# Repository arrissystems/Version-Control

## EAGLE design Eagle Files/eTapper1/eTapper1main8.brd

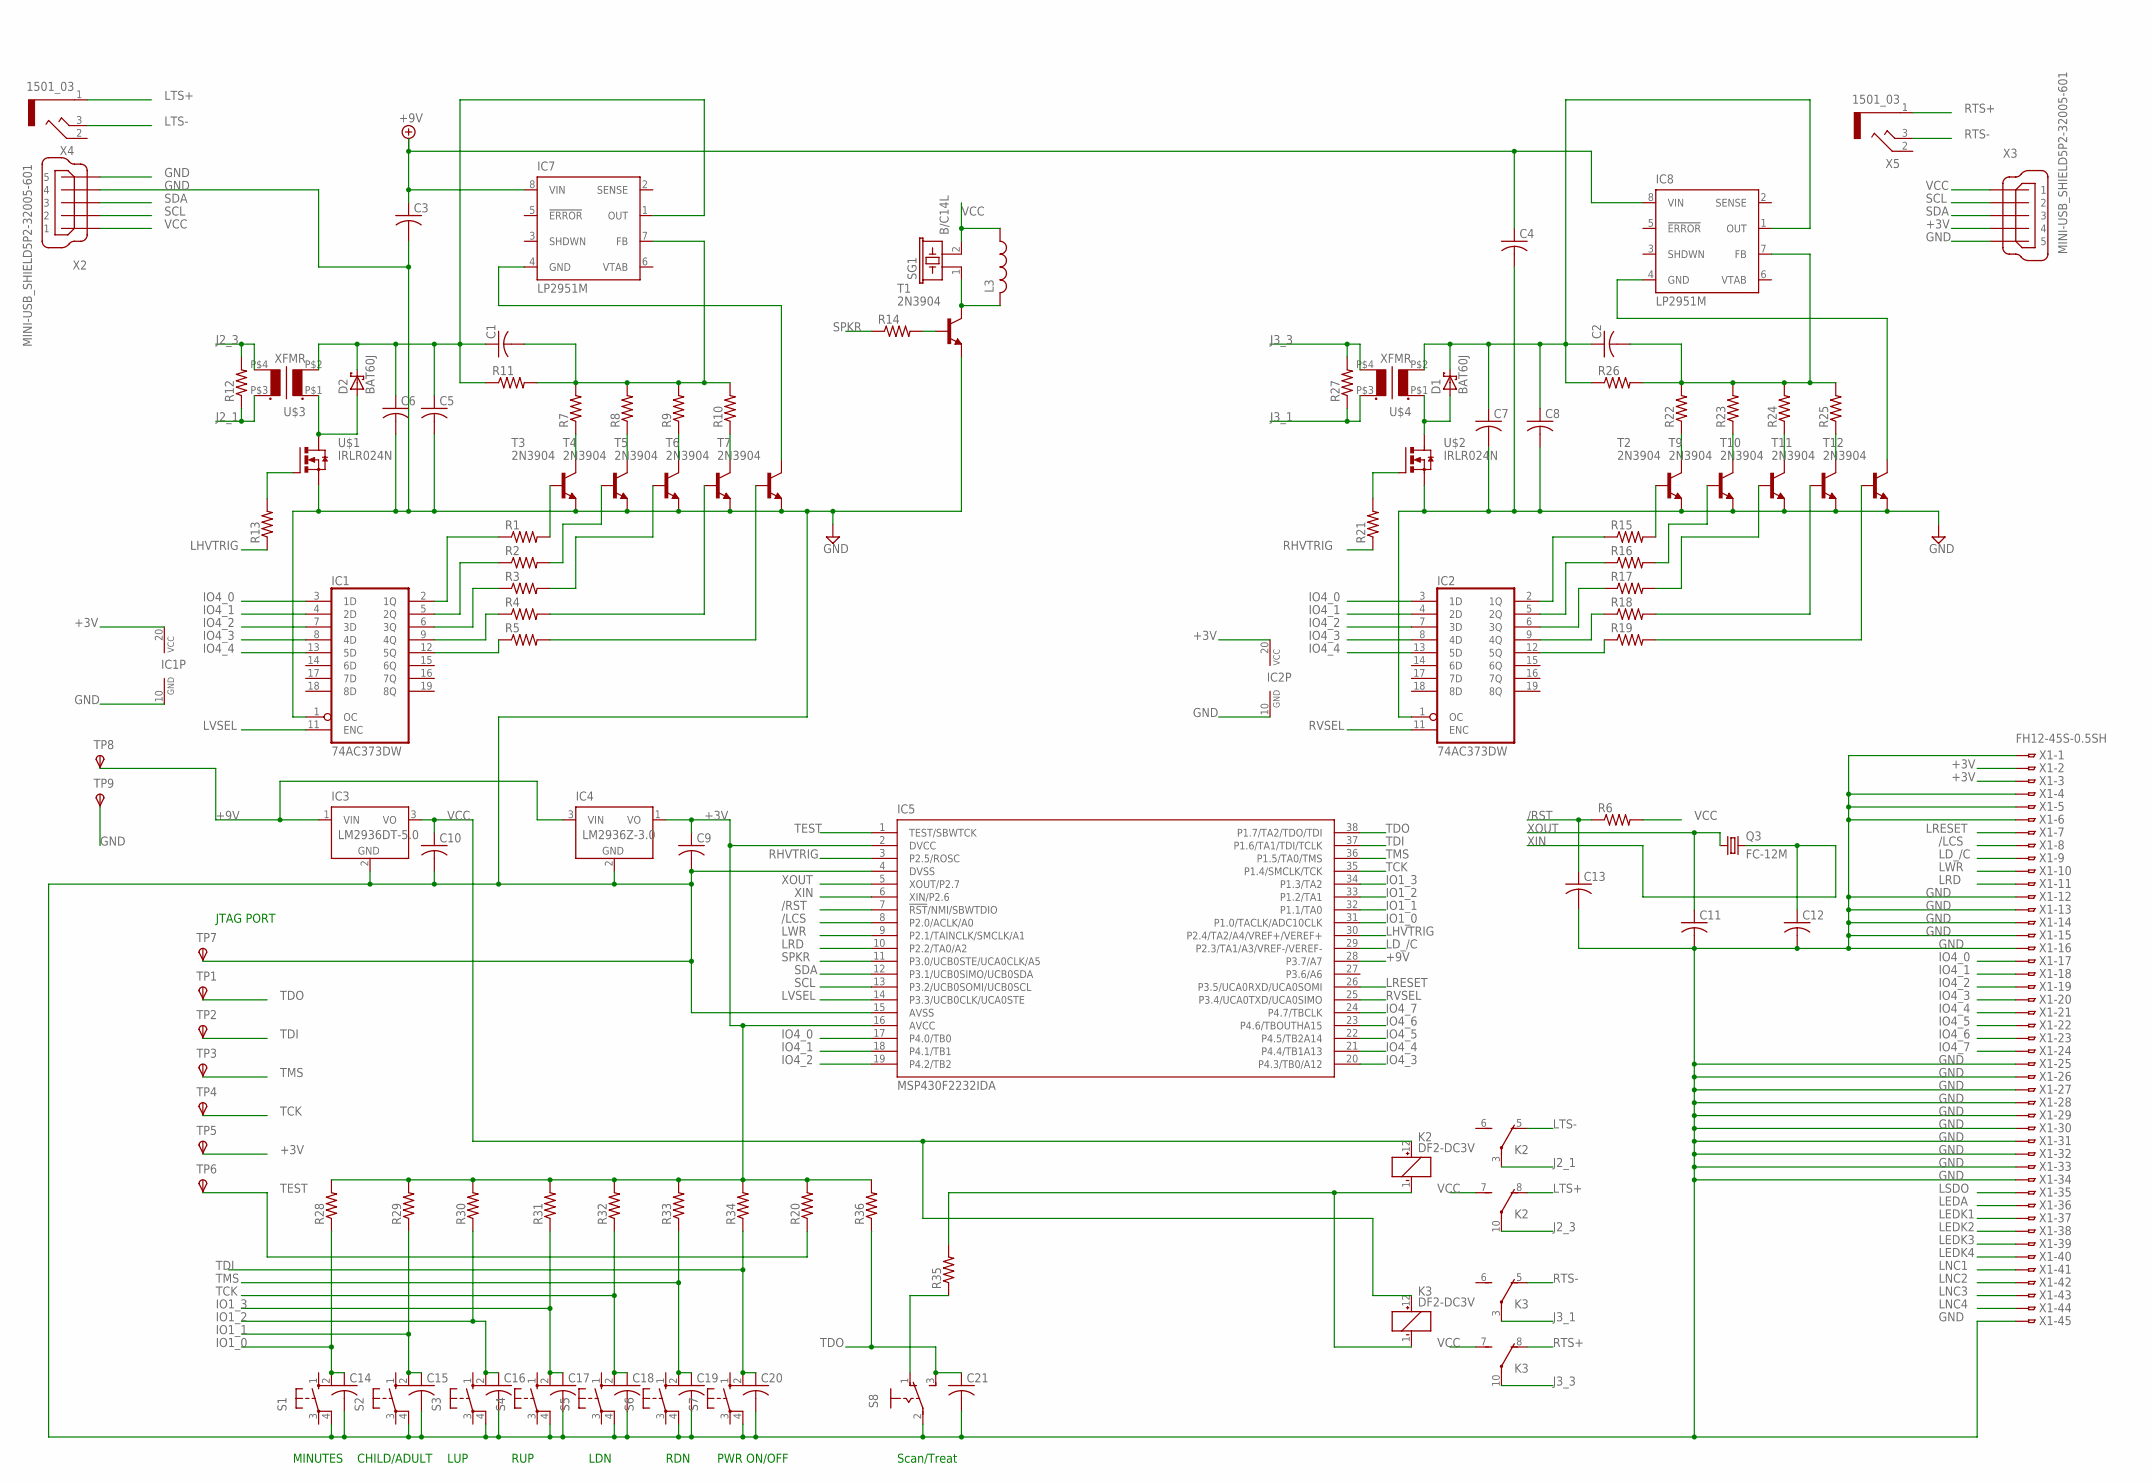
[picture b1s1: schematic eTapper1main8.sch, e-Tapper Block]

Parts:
C1, C2, C3, C4, C5, C6, C7, C8, C9, C10, C11, C12, C13, C14, C15, C16, C17, C18, C19, C20, C21: C-USC0805; C0805
D1, D2: BAT60J; SOD323_ST
IC1, IC2: 74AC373DW; SO20W
IC3: LM2936DT-5.0; TO252
IC4: LM2936Z-3.0; TO92
IC5: MSP430F2232IDA; TSSOP38_R-PDSO-G38-DA
IC7, IC8: LP2951M; SO08
K2, K3: DF2-DC3V; DF2
L3: L-USL2825P; L2825P
Q3: FC-12M
R1, R2, R3, R4, R5, R6, R7, R8, R9, R10, R11, R12, R13, R14, R15, R16, R17, R18, R19, R20, R21, R22, R23, R24, R25, R26, R27, R28, R29, R30, R31, R32, R33, R34, R35, R36: R-US_R0402; R0402
S1, S2, S3, S4, S5, S6, S7: 10-XX; B3F-10XX
S8: M251
SG1: B/C14L
T1, T2, T3, T4, T5, T6, T7, T9, T10, T11, T12: 2N3904; TO92
TP1, TP2, TP3, TP4, TP5, TP6, TP7, TP8, TP9: TPSTP06R; TP06R
U$1, U$2: IRLR024N; I-PAK_TO251AA
U$3, U$4: XFMR
X1: FH12-45S-0.5SH
X2, X3: MINI-USB_SHIELD5P2-32005-601; 32005-601
X4, X5: 1501_03

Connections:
+3V: C9.1, IC1.20 (VCC), IC2.20 (VCC), IC4.1 (VO), IC5.2 (DVCC), IC5.16 (AVCC), R20.2, R28.2, R29.2, R30.2, R31.2, R32.2, R33.2, R34.2, R36.2, TP5.TP, X1.2, X1.3, X3.4
+9V: C3.1, C4.1, IC3.1 (VIN), IC4.3 (VIN), IC5.28 (P3.7/A7), IC7.8 (VIN), IC8.8 (VIN), TP8.TP
/LCS: IC5.8 (P2.0/ACLK/A0), X1.8
/RST: C13.1, IC5.7 (!RST!/NMI/SBWTDIO), R6.1
GND: C3.2, C4.2, C5.2, C6.2, C7.2, C8.2, C9.2, C10.2, C11.2, C12.2, C13.2, C14.2, C15.2, C16.2, C17.2, C18.2, C19.2, C20.2, C21.2, IC1.1 (OC), IC1.10 (GND), IC2.1 (OC), IC2.10 (GND), IC3.2 (GND), IC4.2 (GND), IC5.4 (DVSS), IC5.15 (AVSS), S1.4 (P1), S2.4 (P1), S3.4 (P1), S4.4 (P1), S5.4 (P1), S6.4 (P1), S7.4 (P1), S8.2, T1.3 (E), T2.3 (E), T3.3 (E), T4.3 (E), T5.3 (E), T6.3 (E), T7.3 (E), T9.3 (E), T10.3 (E), T11.3 (E), T12.3 (E), TP7.TP, TP9.TP, U$1.3 (S), U$2.3 (S), X1.1, X1.4, X1.5, X1.6, X1.12, X1.13, X1.14, X1.15, X1.16, X1.25, X1.26, X1.27, X1.28, X1.29, X1.30, X1.31, X1.32, X1.33, X1.34, X1.45, X2.4, X2.5, X3.5
IO1_0: C14.1, IC5.31 (P1.0/TACLK/ADC10CLK), R28.1, S1.2 (S1)
IO1_1: C15.1, IC5.32 (P1.1/TA0), R29.1, S2.2 (S1)
IO1_2: C16.1, IC5.33 (P1.2/TA1), R30.1, S3.2 (S1)
IO1_3: C17.1, IC5.34 (P1.3/TA2), R31.1, S4.2 (S1)
IO4_0: IC1.3 (1D), IC2.3 (1D), IC5.17 (P4.0/TB0), X1.17
IO4_1: IC1.4 (2D), IC2.4 (2D), IC5.18 (P4.1/TB1), X1.18
IO4_2: IC1.7 (3D), IC2.7 (3D), IC5.19 (P4.2/TB2), X1.19
IO4_3: IC1.8 (4D), IC2.8 (4D), IC5.20 (P4.3/TB0/A12), X1.20
IO4_4: IC1.13 (5D), IC2.13 (5D), IC5.21 (P4.4/TB1A13), X1.21
IO4_5: IC5.22 (P4.5/TB2A14), X1.22
IO4_6: IC5.23 (P4.6/TBOUTHA15), X1.23
IO4_7: IC5.24 (P4.7/TBCLK), X1.24
J2_1: K2.3, R12.1, U$3.P$3 (S1)
J2_3: K2.10, R12.2, U$3.P$4 (S2)
J3_1: K3.3, R27.1, U$4.P$3 (S1)
J3_3: K3.10, R27.2, U$4.P$4 (S2)
LD_/C: IC5.29 (P2.3/TA1/A3/VREF-/VEREF-), X1.9
LEDA: X1.36
LEDK1: X1.37
LEDK2: X1.38
LEDK3: X1.39
LEDK4: X1.40
LHVTRIG: IC5.30 (P2.4/TA2/A4/VREF+/VEREF+), R13.1
LNC1: X1.41
LNC2: X1.42
LNC3: X1.43
LNC4: X1.44
LRD: IC5.10 (P2.2/TA0/A2), X1.11
LRESET: IC5.26 (P3.5/UCA0RXD/UCA0SOMI), X1.7
LSDO: X1.35
LTS+: K2.8 (O), X4.1
LTS-: K2.5 (O), X4.3
LVSEL: IC1.11 (ENC), IC5.14 (P3.3/UCB0CLK/UCA0STE)
LWR: IC5.9 (P2.1/TAINCLK/SMCLK/A1), X1.10
unnamed: IC1.2 (1Q), R1.1
unnamed: IC1.5 (2Q), R2.1
unnamed: IC1.6 (3Q), R3.1
unnamed: IC1.9 (4Q), R4.1
unnamed: IC1.12 (5Q), R5.1
unnamed: L3.2, SG1.1, T1.1 (C)
unnamed: R4.2, T6.2 (B)
unnamed: R5.2, T7.2 (B)
unnamed: D2.A, U$1.2 (D), U$1.4 (D), U$3.P$1 (P1)
unnamed: R7.1, T3.1 (C)
unnamed: R8.1, T4.1 (C)
unnamed: R9.1, T5.1 (C)
unnamed: R1.2, T3.2 (B)
unnamed: R2.2, T4.2 (B)
unnamed: R3.2, T5.2 (B)
unnamed: R10.1, T6.1 (C)
unnamed: C1.2, IC7.7 (FB), R7.2, R8.2, R9.2, R10.2, R11.2
unnamed: C1.1, C5.1, C6.1, D2.C, IC7.1 (OUT), R11.1, U$3.P$2 (P2)
unnamed: D1.A, U$2.2 (D), U$2.4 (D), U$4.P$1 (P1)
unnamed: IC2.2 (1Q), R15.1
unnamed: R13.2, U$1.1 (G)
unnamed: R14.2, T1.2 (B)
unnamed: R35.1, S8.1 (O)
unnamed: IC2.5 (2Q), R16.1
unnamed: IC2.6 (3Q), R17.1
unnamed: IC2.9 (4Q), R18.1
unnamed: IC2.12 (5Q), R19.1
unnamed: R15.2, T2.2 (B)
unnamed: R16.2, T9.2 (B)
unnamed: R17.2, T10.2 (B)
unnamed: R18.2, T11.2 (B)
unnamed: R19.2, T12.2 (B)
unnamed: K2.1 (-), K3.1 (-), R35.2
unnamed: R22.1, T2.1 (C)
unnamed: R23.1, T9.1 (C)
unnamed: R24.1, T10.1 (C)
unnamed: R25.1, T11.1 (C)
unnamed: C2.2, IC8.7 (FB), R22.2, R23.2, R24.2, R25.2, R26.2
unnamed: C2.1, C7.1, C8.1, D1.C, IC8.1 (OUT), R26.1, U$4.P$2 (P2)
unnamed: R21.2, U$2.1 (G)
unnamed: IC7.4 (GND), T7.1 (C)
unnamed: IC8.4 (GND), T12.1 (C)
RHVTRIG: IC5.3 (P2.5/ROSC), R21.1
RTS+: K3.8 (O), X5.1
RTS-: K3.5 (O), X5.3
RVSEL: IC2.11 (ENC), IC5.25 (P3.4/UCA0TXD/UCA0SIMO)
SCL: IC5.13 (P3.2/UCB0SOMI/UCB0SCL), X2.2, X3.2
SDA: IC5.12 (P3.1/UCB0SIMO/UCB0SDA), X2.3, X3.3
SPKR: IC5.11 (P3.0/UCB0STE/UCA0CLK/A5), R14.1
TCK: C18.1, IC5.35 (P1.4/SMCLK/TCK), R32.1, S5.2 (S1), TP4.TP
TDI: C20.1, IC5.37 (P1.6/TA1/TDI/TCLK), R34.1, S7.2 (S1), TP2.TP
TDO: C21.1, IC5.38 (P1.7/TA2/TDO/TDI), R36.1, S8.3 (S), TP1.TP
TEST: IC5.1 (TEST/SBWTCK), R20.1, TP6.TP
TMS: C19.1, IC5.36 (P1.5/TA0/TMS), R33.1, S6.2 (S1), TP3.TP
VCC: C10.1, IC3.3 (VO), K2.7 (S), K2.12 (+), K3.7 (S), K3.12 (+), L3.1, R6.2, SG1.2, X2.1, X3.1
XIN: C12.1, IC5.6 (XIN/P2.6), Q3.2
XOUT: C11.1, IC5.5 (XOUT/P2.7), Q3.1

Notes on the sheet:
PWR ON/OFF
Scan/Treat
MINUTES
CHILD/ADULT
LUP
RUP
JTAG PORT
LDN
RDN

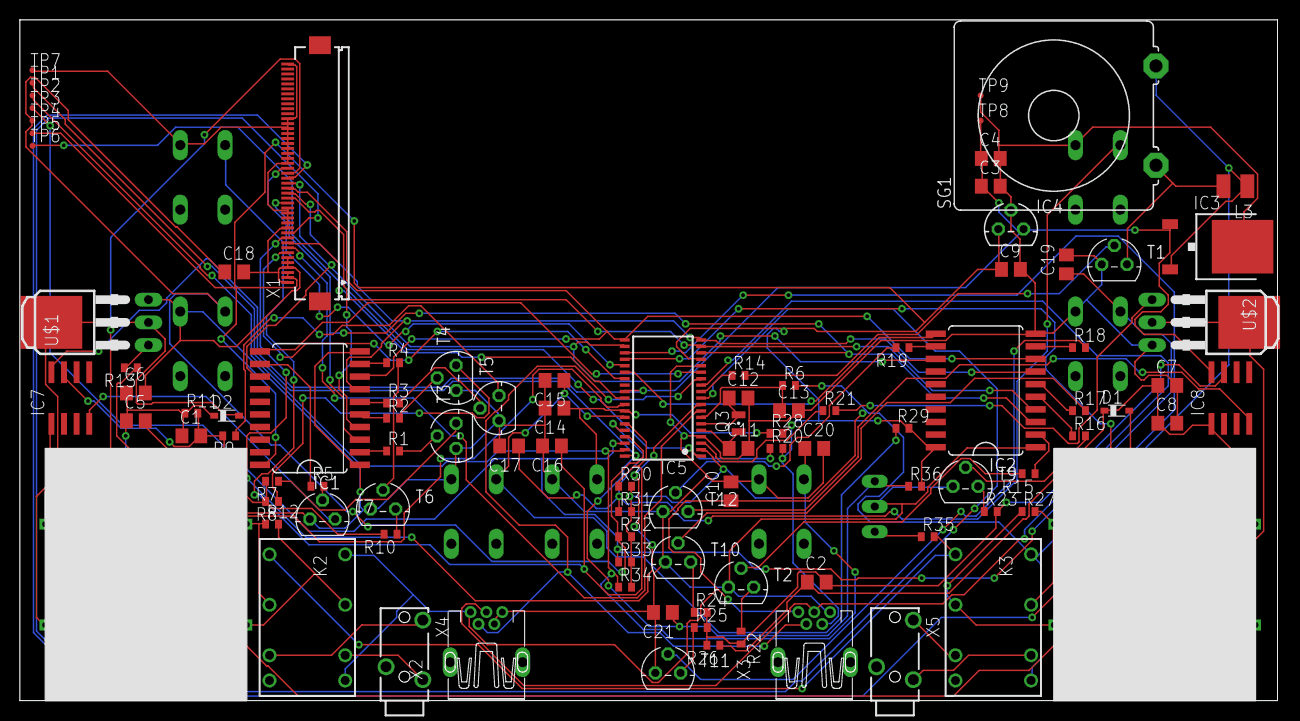
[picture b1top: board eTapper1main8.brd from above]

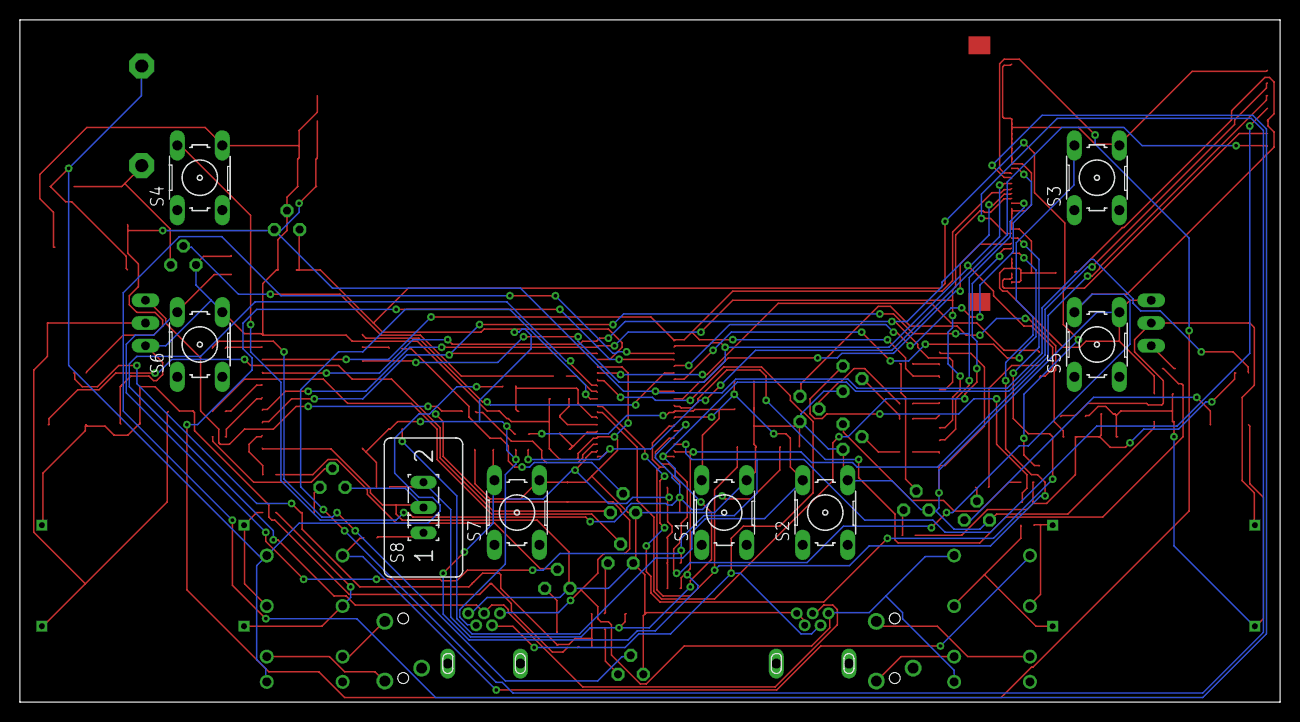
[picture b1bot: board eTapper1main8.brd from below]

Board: 2 copper layers, 126.7 x 68.6 mm, 108 parts (8 on the bottom side), 86 nets.

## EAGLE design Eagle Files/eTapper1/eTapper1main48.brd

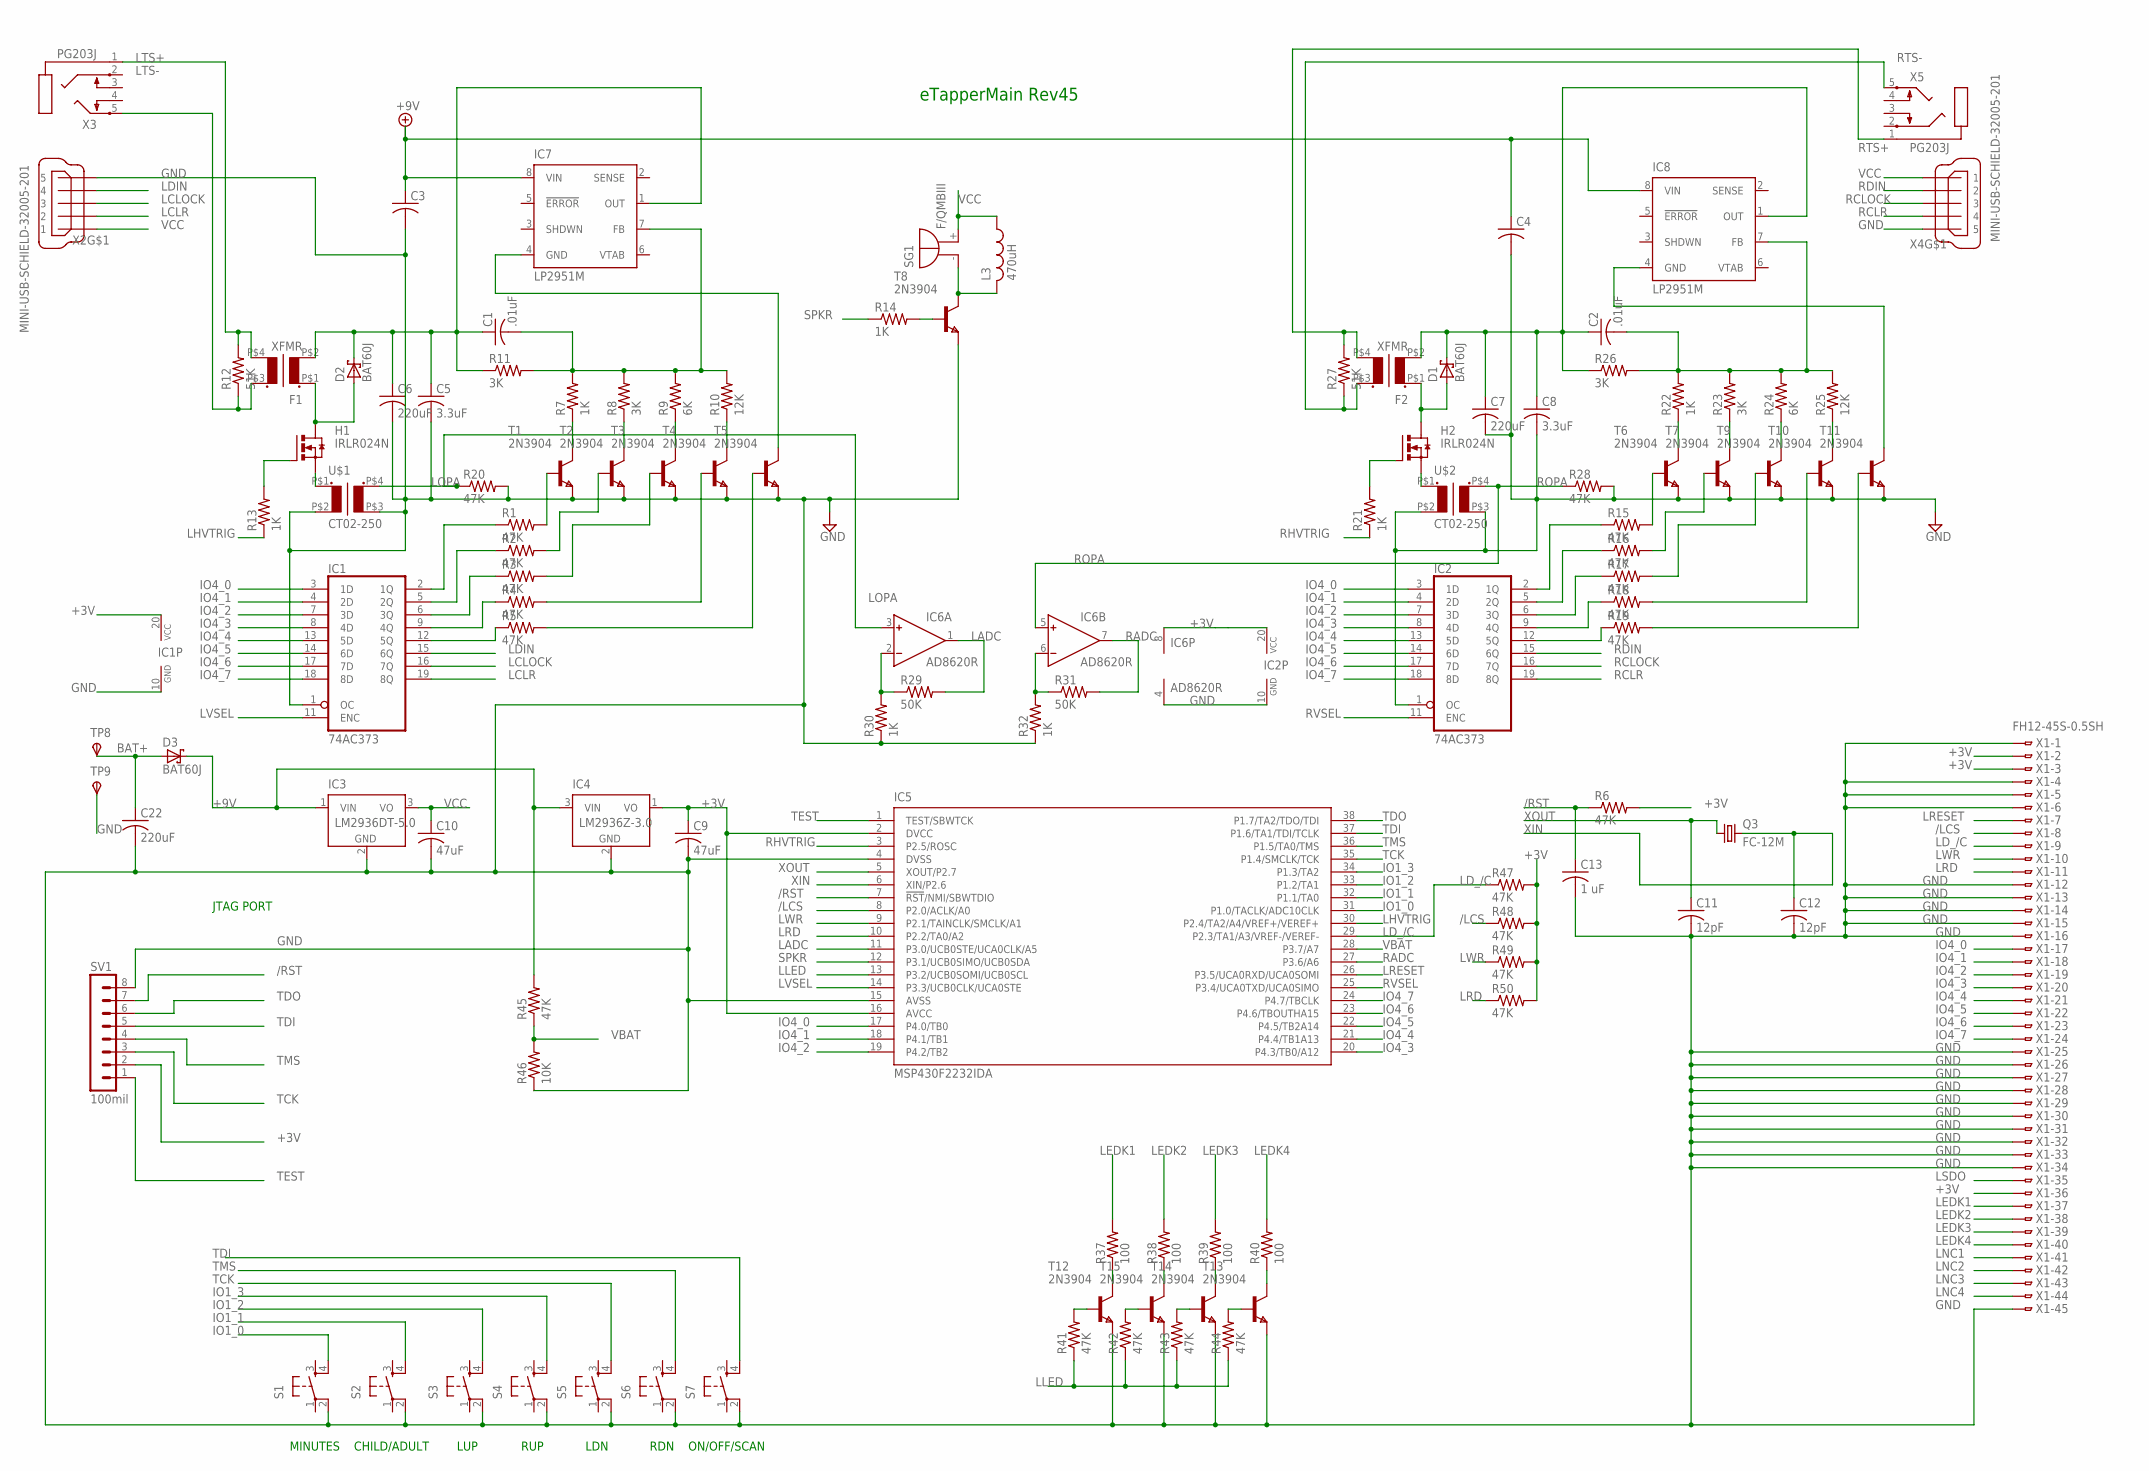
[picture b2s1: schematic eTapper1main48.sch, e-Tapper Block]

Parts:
C1, C2: .01uF; C0805
C3, C4: C-USC1206; C1206
C5, C8: 3.3uF; C0805
C6, C7, C22: 220uF; C1206
C9, C10: 47uF; C1206
C11, C12: 12pF; C0805
C13: 1 uF; C0805
D1, D2, D3: BAT60J; SOD323_ST
F1, F2: XFMR
H1, H2: IRLR024N; D-PAK_TO252AA
IC1, IC2: 74AC373; SO20
IC3: LM2936DT-5.0; TO252
IC4: LM2936Z-3.0; TO92
IC5: MSP430F2232IDA; TSSOP38_R-PDSO-G38-DA
IC6: AD8620R; SO8
IC7, IC8: LP2951M; SO08
L3: 470uH; L2825P
Q3: FC-12M
R1, R2, R3, R4, R5, R6, R15, R16, R17, R18, R19, R20, R28, R41, R42, R43, R44, R45, R47, R48, R49, R50: 47K; R0402
R7, R13, R14, R21, R22, R30, R32: 1K; R0402
R8, R11, R23, R26: 3K; R0402
R9, R24: 6K; R0402
R10, R25: 12K; R0402
R12, R27: 51K; R0402
R29, R31: 50K; R0402
R37, R38, R39, R40: 100; R0402
R46: 10K; R0402
S1, S2, S3, S4, S5, S6, S7: 10-XX; B3F-10XX
SG1: F/QMBIII
SV1: 100mil; MA08-1
T1, T2, T3, T4, T5, T6, T7, T8, T9, T10, T11, T12, T13, T14, T15: 2N3904; SOT-23
TP8, TP9: TPSPAD1-20; P1-20
U$1, U$2: CT02-250
X1: FH12-45S-0.5SH
X2, X4: MINI-USB-SCHIELD-32005-201; 32005-201
X3, X5: PG203J

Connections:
+3V: C9.1, IC1.20 (VCC), IC2.20 (VCC), IC4.1 (VO), IC5.2 (DVCC), IC5.16 (AVCC), IC6.8 (V+), R6.2, R47.2, R48.2, R49.2, R50.2, SV1.2, X1.2, X1.3, X1.36
+9V: C3.1, C4.1, D3.C, IC3.1 (VIN), IC4.3 (VIN), IC7.8 (VIN), IC8.8 (VIN), R45.2
/LCS: IC5.8 (P2.0/ACLK/A0), R48.1, X1.8
/RST: C13.1, IC5.7 (!RST!/NMI/SBWTDIO), R6.1, SV1.7
BAT+: C22.1, D3.A, TP8.TP
GND: C3.2, C4.2, C5.2, C6.2, C7.2, C8.2, C9.2, C10.2, C11.2, C12.2, C13.2, C22.2, IC1.1 (OC), IC1.10 (GND), IC2.1 (OC), IC2.10 (GND), IC3.2 (GND), IC4.2 (GND), IC5.4 (DVSS), IC5.15 (AVSS), IC6.4 (V-), R20.2, R28.2, R30.1, R32.1, R46.1, S1.2 (P1), S2.2 (P1), S3.2 (P1), S4.2 (P1), S5.2 (P1), S6.2 (P1), S7.2 (P1), SV1.8, T1.2 (E), T2.2 (E), T3.2 (E), T4.2 (E), T5.2 (E), T6.2 (E), T7.2 (E), T8.2 (E), T9.2 (E), T10.2 (E), T11.2 (E), T12.2 (E), T13.2 (E), T14.2 (E), T15.2 (E), TP9.TP, U$1.P$2 (P2), U$1.P$3 (S2), U$2.P$2 (P2), U$2.P$3 (S2), X1.1, X1.4, X1.5, X1.6, X1.12, X1.13, X1.14, X1.15, X1.16, X1.25, X1.26, X1.27, X1.28, X1.29, X1.30, X1.31, X1.32, X1.33, X1.34, X1.45, X2.5, X4.5
IO1_0: IC5.31 (P1.0/TACLK/ADC10CLK), S1.4 (S1)
IO1_1: IC5.32 (P1.1/TA0), S2.4 (S1)
IO1_2: IC5.33 (P1.2/TA1), S3.4 (S1)
IO1_3: IC5.34 (P1.3/TA2), S4.4 (S1)
IO4_0: IC1.3 (1D), IC2.3 (1D), IC5.17 (P4.0/TB0), X1.17
IO4_1: IC1.4 (2D), IC2.4 (2D), IC5.18 (P4.1/TB1), X1.18
IO4_2: IC1.7 (3D), IC2.7 (3D), IC5.19 (P4.2/TB2), X1.19
IO4_3: IC1.8 (4D), IC2.8 (4D), IC5.20 (P4.3/TB0/A12), X1.20
IO4_4: IC1.13 (5D), IC2.13 (5D), IC5.21 (P4.4/TB1A13), X1.21
IO4_5: IC1.14 (6D), IC2.14 (6D), IC5.22 (P4.5/TB2A14), X1.22
IO4_6: IC1.17 (7D), IC2.17 (7D), IC5.23 (P4.6/TBOUTHA15), X1.23
IO4_7: IC1.18 (8D), IC2.18 (8D), IC5.24 (P4.7/TBCLK), X1.24
LADC: IC5.11 (P3.0/UCB0STE/UCA0CLK/A5), IC6.1 (OUT), R29.2
LCLOCK: IC1.16 (7Q), X2.3
LCLR: IC1.19 (8Q), X2.2
LDIN: IC1.15 (6Q), X2.4
LD_/C: IC5.29 (P2.3/TA1/A3/VREF-/VEREF-), R47.1, X1.9
LEDK1: R37.2, X1.37
LEDK2: R38.2, X1.38
LEDK3: R39.2, X1.39
LEDK4: R40.2, X1.40
LHVTRIG: IC5.30 (P2.4/TA2/A4/VREF+/VEREF+), R13.1
LLED: IC5.13 (P3.2/UCB0SOMI/UCB0SCL), R41.1, R42.1, R43.1, R44.1
LNC1: X1.41
LNC2: X1.42
LNC3: X1.43
LNC4: X1.44
LOPA: IC6.3 (IN+), R20.1, U$1.P$4 (S1)
LRD: IC5.10 (P2.2/TA0/A2), R50.1, X1.11
LRESET: IC5.26 (P3.5/UCA0RXD/UCA0SOMI), X1.7
LSDO: X1.35
LTS+: F1.P$4 (S2), R12.2, X3.1
LTS-: F1.P$3 (S1), R12.1, X3.5
LVSEL: IC1.11 (ENC), IC5.14 (P3.3/UCB0CLK/UCA0STE)
LWR: IC5.9 (P2.1/TAINCLK/SMCLK/A1), R49.1, X1.10
unnamed: IC1.2 (1Q), R1.1
unnamed: IC1.5 (2Q), R2.1
unnamed: IC1.6 (3Q), R3.1
unnamed: IC1.9 (4Q), R4.1
unnamed: IC1.12 (5Q), R5.1
unnamed: L3.2, SG1.- (+), T8.1 (C)
unnamed: R4.2, T4.3 (B)
unnamed: R5.2, T5.3 (B)
unnamed: D2.A, F1.P$1 (P1), H1.4 (D)
unnamed: R7.1, T1.1 (C)
unnamed: R8.1, T2.1 (C)
unnamed: R9.1, T3.1 (C)
unnamed: R1.2, T1.3 (B)
unnamed: R2.2, T2.3 (B)
unnamed: R3.2, T3.3 (B)
unnamed: R10.1, T4.1 (C)
unnamed: C1.2, IC7.7 (FB), R7.2, R8.2, R9.2, R10.2, R11.2
unnamed: C1.1, C5.1, C6.1, D2.C, F1.P$2 (P2), IC7.1 (OUT), R11.1
unnamed: D1.A, F2.P$1 (P1), H2.4 (D)
unnamed: IC2.2 (1Q), R15.1
unnamed: H1.1 (G), R13.2
unnamed: R14.2, T8.3 (B)
unnamed: H1.3 (S), U$1.P$1 (P1)
unnamed: IC2.5 (2Q), R16.1
unnamed: IC2.6 (3Q), R17.1
unnamed: IC2.9 (4Q), R18.1
unnamed: IC2.12 (5Q), R19.1
unnamed: R44.2, T13.3 (B)
unnamed: R15.2, T6.3 (B)
unnamed: R16.2, T7.3 (B)
unnamed: R17.2, T9.3 (B)
unnamed: R18.2, T10.3 (B)
unnamed: R19.2, T11.3 (B)
unnamed: R22.1, T6.1 (C)
unnamed: R23.1, T7.1 (C)
unnamed: R24.1, T9.1 (C)
unnamed: R25.1, T10.1 (C)
unnamed: C2.2, IC8.7 (FB), R22.2, R23.2, R24.2, R25.2, R26.2
unnamed: C2.1, C7.1, C8.1, D1.C, F2.P$2 (P2), IC8.1 (OUT), R26.1
unnamed: R37.1, T12.1 (C)
unnamed: H2.1 (G), R21.2
unnamed: R38.1, T15.1 (C)
unnamed: R39.1, T14.1 (C)
unnamed: IC7.4 (GND), T5.1 (C)
unnamed: R40.1, T13.1 (C)
unnamed: IC8.4 (GND), T11.1 (C)
unnamed: R43.2, T14.3 (B)
unnamed: R41.2, T12.3 (B)
unnamed: R42.2, T15.3 (B)
unnamed: H2.3 (S), U$2.P$1 (P1)
unnamed: IC6.6 (IN-), R31.1, R32.2
unnamed: IC6.2 (IN-), R29.1, R30.2
RADC: IC5.27 (P3.6/A6), IC6.7 (OUT), R31.2
RCLOCK: IC2.16 (7Q), X4.3
RCLR: IC2.19 (8Q), X4.4
RDIN: IC2.15 (6Q), X4.2
RHVTRIG: IC5.3 (P2.5/ROSC), R21.1
ROPA: IC6.5 (IN+), R28.1, U$2.P$4 (S1)
RTS+: F2.P$4 (S2), R27.2, X5.1
RTS-: F2.P$3 (S1), R27.1, X5.5
RVSEL: IC2.11 (ENC), IC5.25 (P3.4/UCA0TXD/UCA0SIMO)
SPKR: IC5.12 (P3.1/UCB0SIMO/UCB0SDA), R14.1
TCK: IC5.35 (P1.4/SMCLK/TCK), S5.4 (S1), SV1.3
TDI: IC5.37 (P1.6/TA1/TDI/TCLK), S7.4 (S1), SV1.5
TDO: IC5.38 (P1.7/TA2/TDO/TDI), SV1.6
TEST: IC5.1 (TEST/SBWTCK), SV1.1
TMS: IC5.36 (P1.5/TA0/TMS), S6.4 (S1), SV1.4
VBAT: IC5.28 (P3.7/A7), R45.1, R46.2
VCC: C10.1, IC3.3 (VO), L3.1, SG1.+ (-), X2.1, X4.1
XIN: C12.1, IC5.6 (XIN/P2.6), Q3.2
XOUT: C11.1, IC5.5 (XOUT/P2.7), Q3.1

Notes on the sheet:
ON/OFF/SCAN
MINUTES
CHILD/ADULT
LUP
RUP
JTAG PORT
LDN
RDN
eTapperMain Rev45

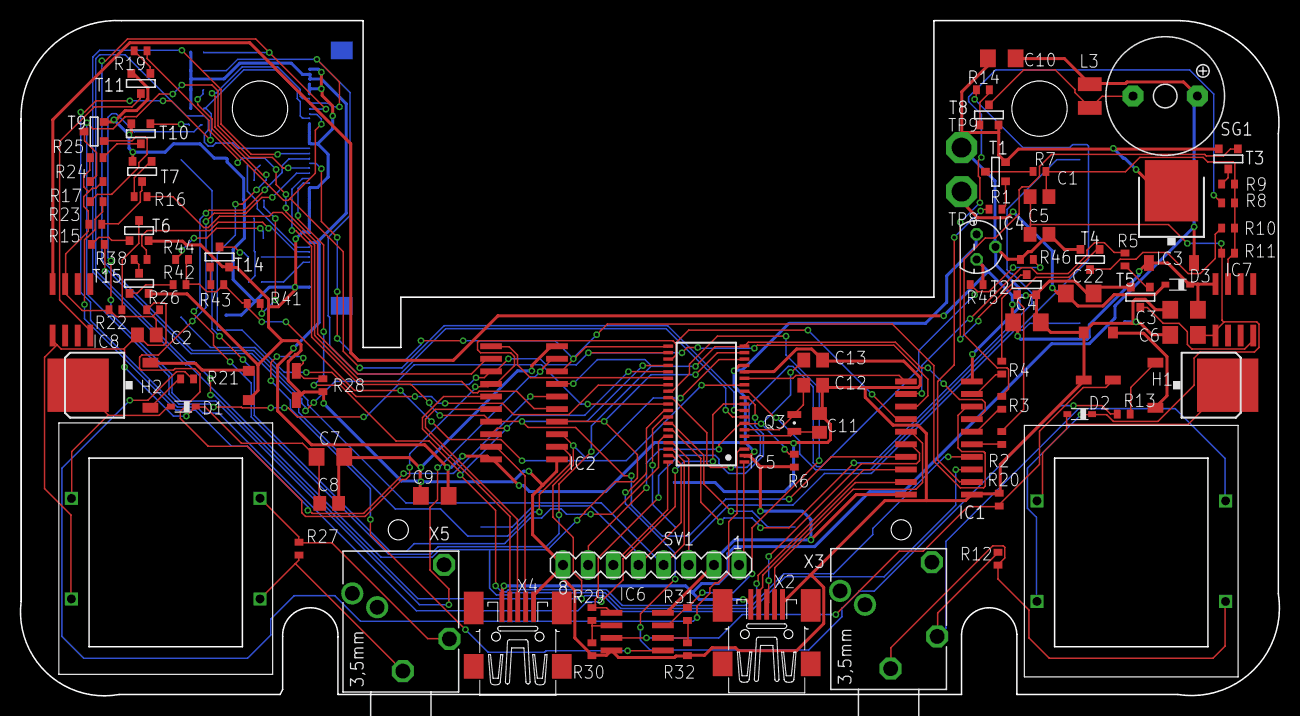
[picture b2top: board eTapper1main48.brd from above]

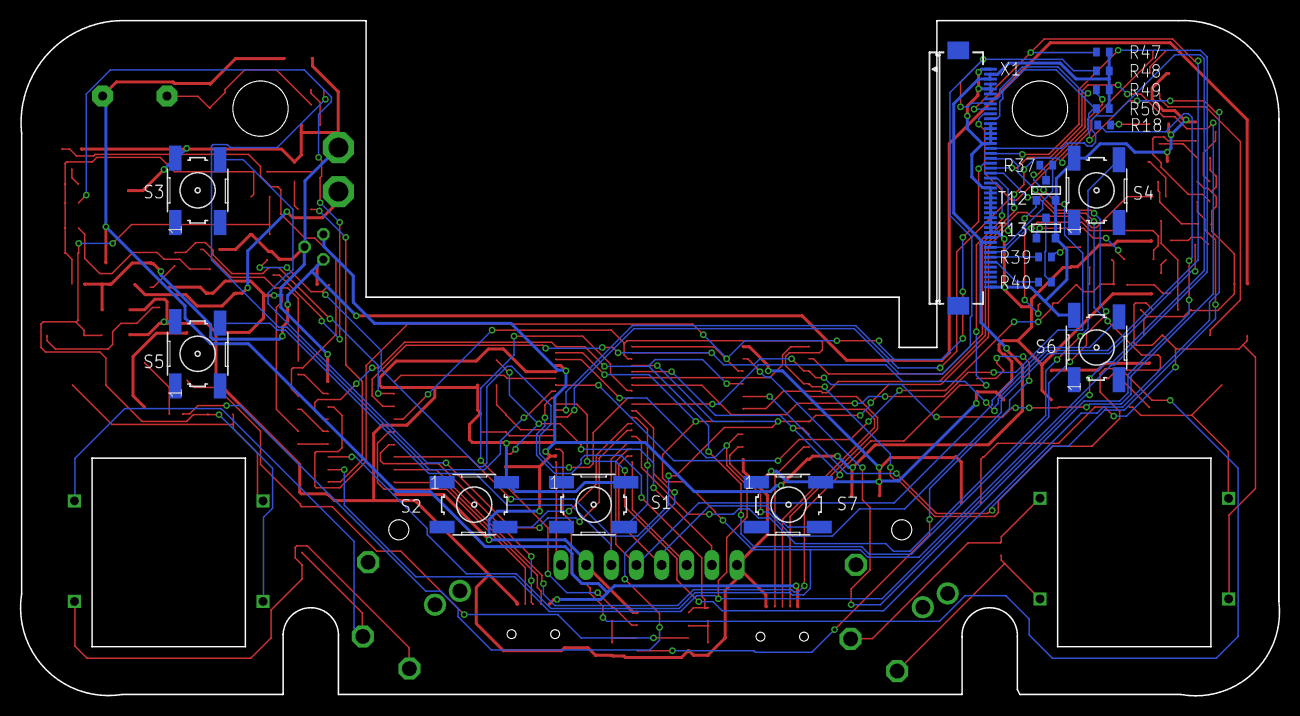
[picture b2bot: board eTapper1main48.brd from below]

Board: 2 copper layers, 127.2 x 68.2 mm, 111 parts (18 on the bottom side), 107 nets.

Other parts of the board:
DRILEGEND: DRILEGEND

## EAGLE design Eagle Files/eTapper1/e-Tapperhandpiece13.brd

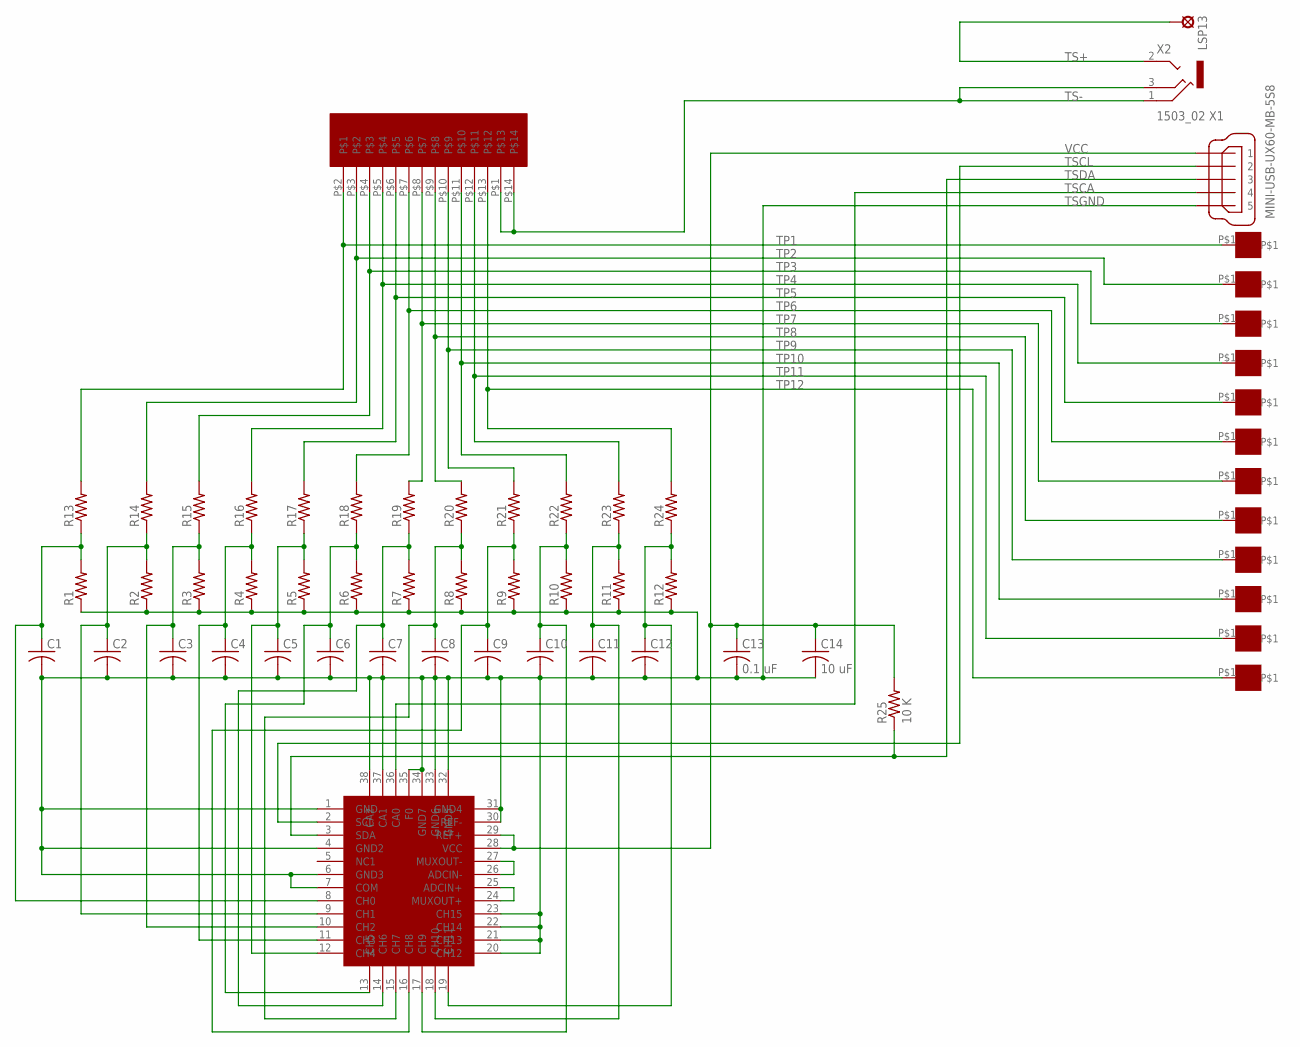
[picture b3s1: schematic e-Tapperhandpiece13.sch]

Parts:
C1, C2, C3, C4, C5, C6, C7, C8, C9, C10, C11, C12: C-USC0603; C0603
C13: 0.1 uF; C0603
C14: 10 uF; C0805
LSP13: SE11
R1, R2, R3, R4, R5, R6, R7, R8, R9, R10, R11, R12, R13, R14, R15, R16, R17, R18, R19, R20, R21, R22, R23, R24: R-US_R0402; R0402
R25: 10 K; R0402
TSP1, TSP2, TSP3, TSP4, TSP5, TSP6, TSP7, TSP8, TSP9, TSP10, TSP11, TSP12: ET1
U$1: LTC2497; QFN38-5X7
U$2: SS112D01
X1: MINI-USB-UX60-MB-5S8; UX60-MB-5S8
X2: 1503_02

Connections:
unnamed: C9.1, R9.2, R21.1, U$1.16 (CH8)
unnamed: U$1.26 (ADCIN-), U$1.27 (MUXOUT-)
unnamed: U$1.24 (MUXOUT+), U$1.25 (ADCIN+)
unnamed: C12.1, R12.2, R24.1, U$1.19 (CH11)
unnamed: C4.1, R4.2, R16.1, U$1.11 (CH3)
unnamed: C10.1, R10.2, R22.1, U$1.17 (CH9)
unnamed: C8.1, R8.2, R20.1, U$1.15 (CH7)
unnamed: C5.1, R5.2, R17.1, U$1.12 (CH4)
unnamed: C6.1, R6.2, R18.1, U$1.13 (CH5)
unnamed: C7.1, R7.2, R19.1, U$1.14 (CH6)
unnamed: C3.1, R3.2, R15.1, U$1.10 (CH2)
unnamed: C2.1, R2.2, R14.1, U$1.9 (CH1)
unnamed: C11.1, R11.2, R23.1, U$1.18 (CH10)
unnamed: C1.1, R1.2, R13.1, U$1.8 (CH0)
TP1: R13.2, TSP1.P$1, U$2.P$2
TP2: R14.2, TSP2.P$1, U$2.P$3
TP3: R15.2, TSP3.P$1, U$2.P$4
TP4: R16.2, TSP4.P$1, U$2.P$5
TP5: R17.2, TSP5.P$1, U$2.P$6
TP6: R18.2, TSP6.P$1, U$2.P$7
TP7: R19.2, TSP7.P$1, U$2.P$8
TP8: R20.2, TSP8.P$1, U$2.P$9
TP9: R21.2, TSP9.P$1, U$2.P$10
TP10: R22.2, TSP10.P$1, U$2.P$11
TP11: R23.2, TSP11.P$1, U$2.P$12
TP12: R24.2, TSP12.P$1, U$2.P$13
TS+: LSP13.MP, X2.2
TS-: U$2.P$1, U$2.P$14, X2.1, X2.3
TSCA: U$1.36 (CA0), X1.4
TSCL: U$1.2 (SCL), X1.2
TSDA: R25.1, U$1.3 (SDA), X1.3
TSGND: C1.2, C2.2, C3.2, C4.2, C5.2, C6.2, C7.2, C8.2, C9.2, C10.2, C11.2, C12.2, C13.2, C14.2, R1.1, R2.1, R3.1, R4.1, R5.1, R6.1, R7.1, R8.1, R9.1, R10.1, R11.1, R12.1, U$1.1 (GND), U$1.4 (GND2), U$1.6 (GND3), U$1.7 (COM), U$1.20 (CH12), U$1.21 (CH13), U$1.22 (CH14), U$1.23 (CH15), U$1.30 (REF-), U$1.31 (GND4), U$1.32 (GND5), U$1.33 (GND6), U$1.34 (GND7), U$1.35 (F0), U$1.37 (CA1), U$1.38 (CA2), X1.5
VCC: C13.1, C14.1, R25.2, U$1.28 (VCC), U$1.29 (REF+), X1.1

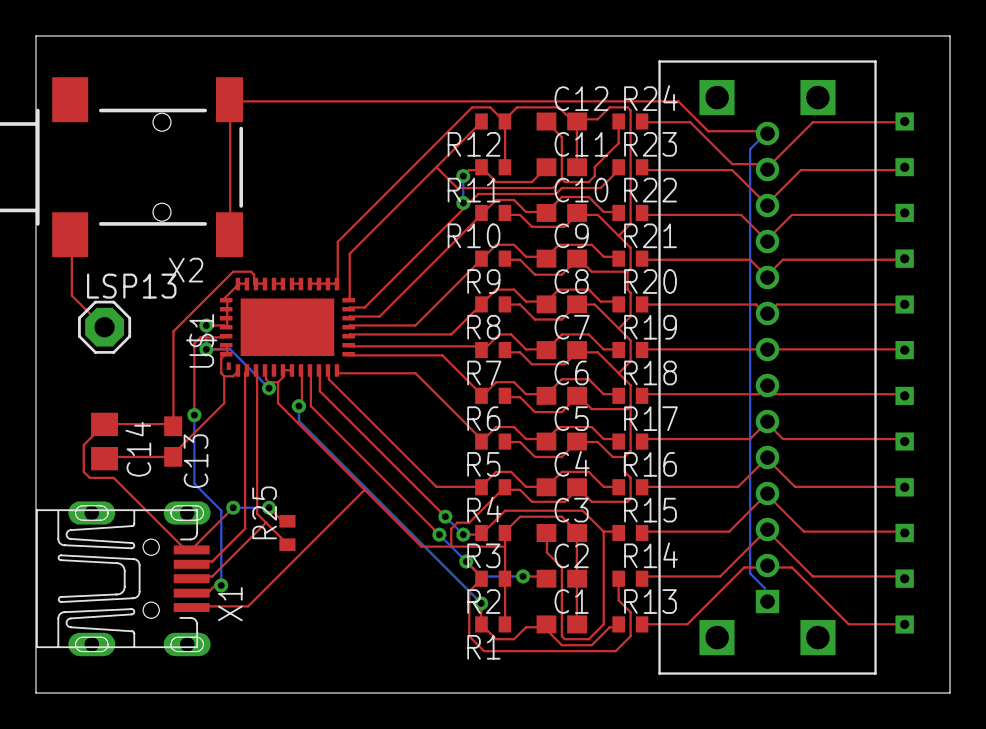
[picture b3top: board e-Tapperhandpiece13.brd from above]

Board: 2 copper layers, 50.8 x 36.5 mm, 56 parts (0 on the bottom side), 33 nets.

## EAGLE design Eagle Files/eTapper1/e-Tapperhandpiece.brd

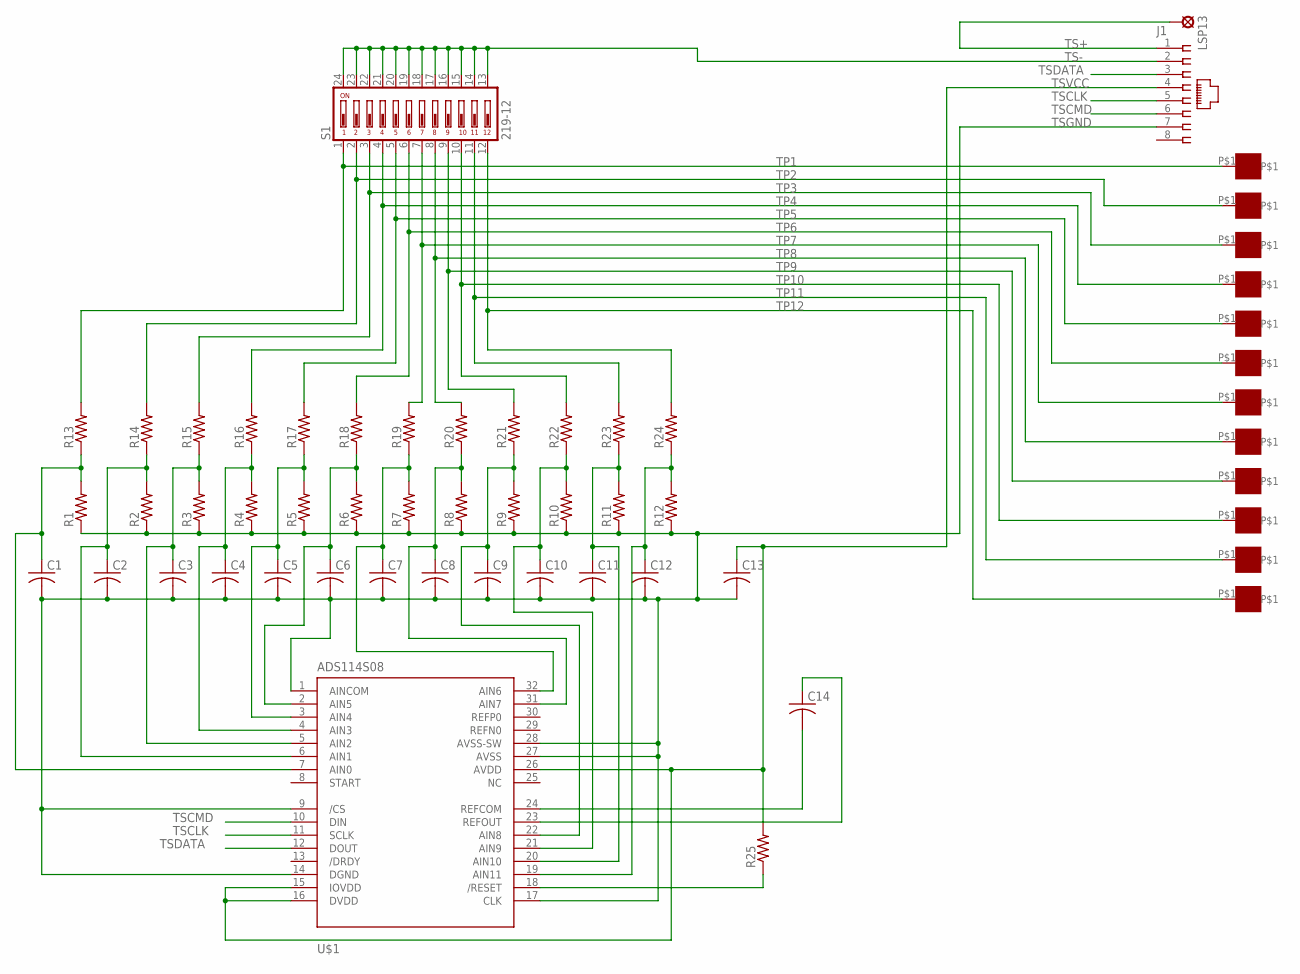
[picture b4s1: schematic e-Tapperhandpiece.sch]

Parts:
C1, C2, C3, C4, C5, C6, C7, C8, C9, C10, C11, C12, C13, C14: C-USC0805; C0805
J1: 215877-4
LSP13: SE11
R1, R2, R3, R4, R5, R6, R7, R8, R9, R10, R11, R12, R13, R14, R15, R16, R17, R18, R19, R20, R21, R22, R23, R24, R25: R-US_R0402; R0402
S1: 219-12; CTS-219-12
TSP1, TSP2, TSP3, TSP4, TSP5, TSP6, TSP7, TSP8, TSP9, TSP10, TSP11, TSP12: ET1
U$1: ADS114S08; TQFP32-08

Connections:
unnamed: R25.1, U$1.18 (/RESET)
unnamed: C1.1, R1.2, R13.1, U$1.7 (AIN0)
unnamed: C2.1, R2.2, R14.1, U$1.6 (AIN1)
unnamed: C3.1, R3.2, R15.1, U$1.5 (AIN2)
unnamed: C4.1, R4.2, R16.1, U$1.4 (AIN3)
unnamed: C5.1, R5.2, R17.1, U$1.3 (AIN4)
unnamed: C6.1, R6.2, R18.1, U$1.2 (AIN5)
unnamed: C7.1, R7.2, R19.1, U$1.32 (AIN6)
unnamed: C8.1, R8.2, R20.1, U$1.31 (AIN7)
unnamed: C9.1, R9.2, R21.1, U$1.22 (AIN8)
unnamed: C10.1, R10.2, R22.1, U$1.21 (AIN9)
unnamed: C11.1, R11.2, R23.1, U$1.20 (AIN10)
unnamed: C12.1, R12.2, R24.1, U$1.19 (AIN11)
REFCOM: C14.2, U$1.24 (REFCOM)
REFOUT: C14.1, U$1.23 (REFOUT)
TP1: R13.2, S1.1, TSP1.P$1
TP2: R14.2, S1.2, TSP2.P$1
TP3: R15.2, S1.3, TSP3.P$1
TP4: R16.2, S1.4, TSP4.P$1
TP5: R17.2, S1.5, TSP5.P$1
TP6: R18.2, S1.6, TSP6.P$1
TP7: R19.2, S1.7, TSP7.P$1
TP8: R20.2, S1.8, TSP8.P$1
TP9: R21.2, S1.9, TSP9.P$1
TP10: R22.2, S1.10, TSP10.P$1
TP11: R23.2, S1.11, TSP11.P$1
TP12: R24.2, S1.12, TSP12.P$1
TS+: J1.1, LSP13.MP
TS-: J1.2, S1.13, S1.14, S1.15, S1.16, S1.17, S1.18, S1.19, S1.20, S1.21, S1.22, S1.23, S1.24
TSCLK: J1.5, U$1.11 (SCLK)
TSCMD: J1.6, U$1.10 (DIN)
TSDATA: J1.3, U$1.12 (DOUT)
TSGND: C1.2, C2.2, C3.2, C4.2, C5.2, C6.2, C7.2, C8.2, C9.2, C10.2, C11.2, C12.2, C13.2, J1.7, R1.1, R2.1, R3.1, R4.1, R5.1, R6.1, R7.1, R8.1, R9.1, R10.1, R11.1, R12.1, U$1.1 (AINCOM), U$1.9 (/CS), U$1.14 (DGND), U$1.17 (CLK), U$1.27 (AVSS), U$1.28 (AVSS-SW)
TSVCC: C13.1, J1.4, R25.2, U$1.15 (IOVDD), U$1.16 (DVDD), U$1.26 (AVDD)

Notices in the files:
Eagle Files/eTapper1/e-Tapperhandpiece31.brd:
e-Tapper Handpiece R31 @All rights reserved
